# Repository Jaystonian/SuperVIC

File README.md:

# SuperVIC
The ultimate hobby computer

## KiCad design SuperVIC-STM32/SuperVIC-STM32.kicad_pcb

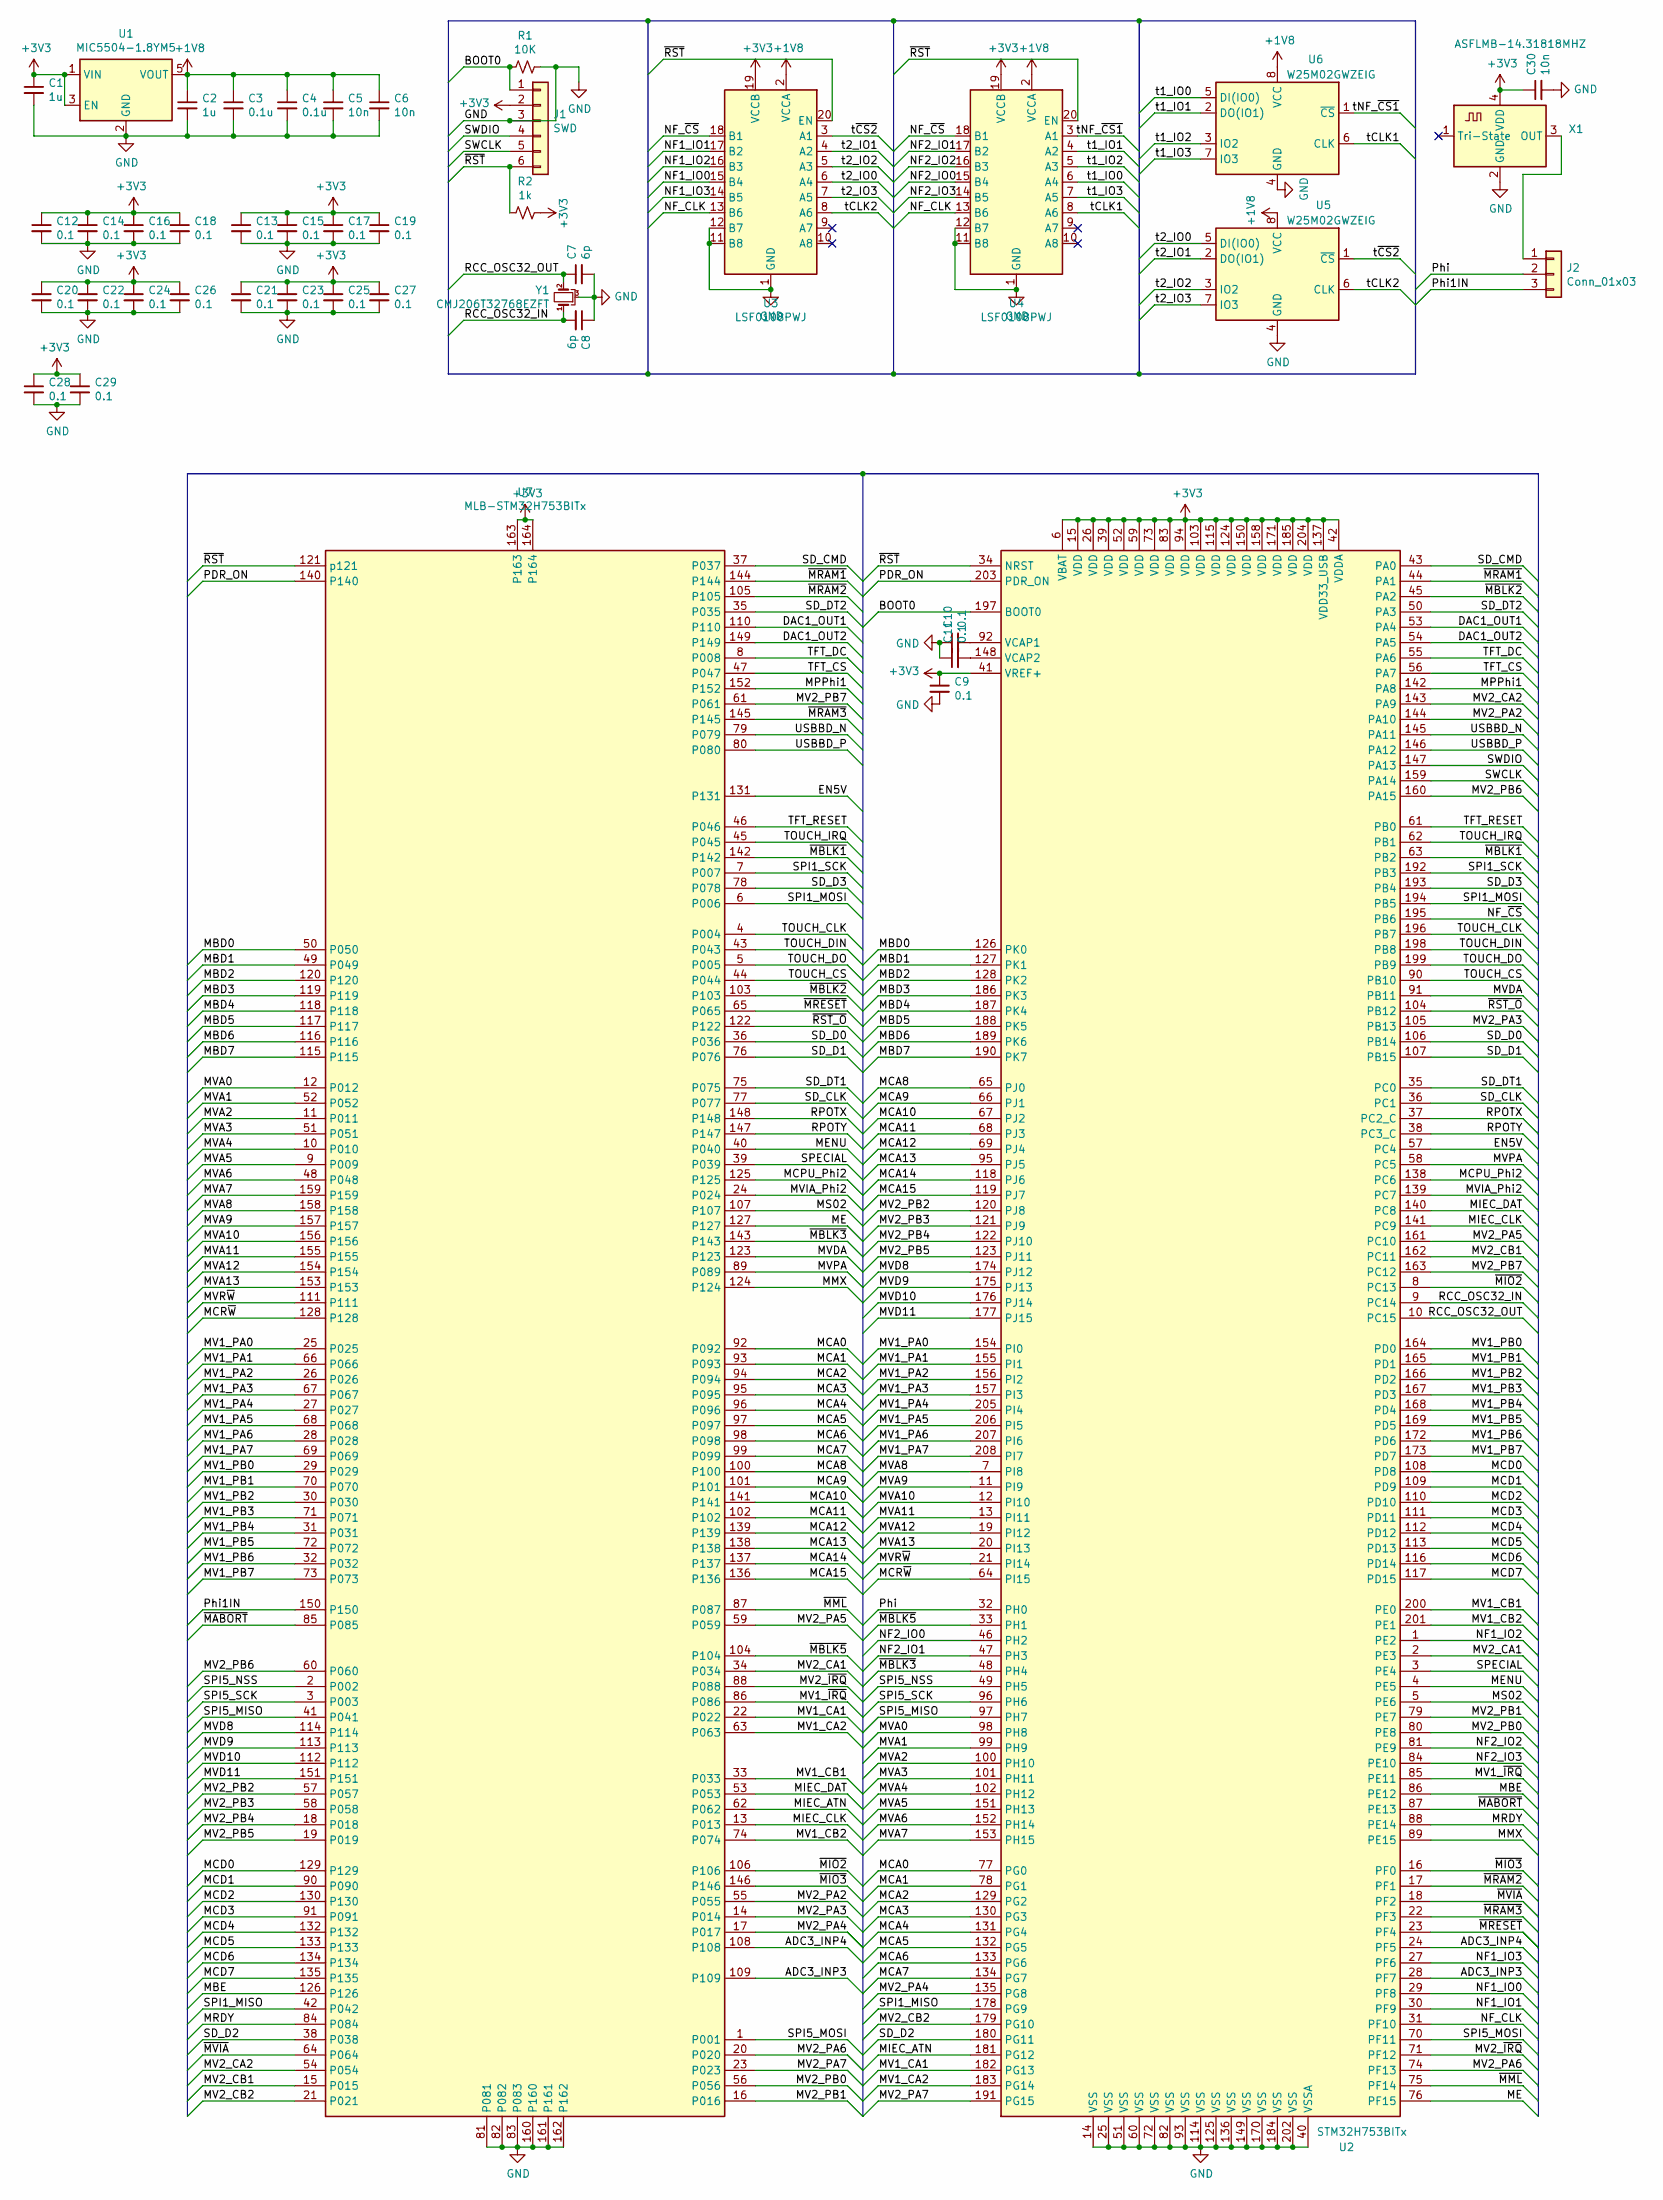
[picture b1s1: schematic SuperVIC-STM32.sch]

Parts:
C1, C2: 1u; C_0805_2012Metric_Pad1.15x1.40mm_HandSolder
C3, C4: 0.1u; C_0805_2012Metric_Pad1.15x1.40mm_HandSolder
C5, C6, C30: 10n; C_0805_2012Metric_Pad1.15x1.40mm_HandSolder
C7, C8: 6p; C_0805_2012Metric_Pad1.15x1.40mm_HandSolder
C9, C10, C11, C12, C13, C14, C15, C16, C17, C18, C19, C20, C21, C22, C23, C24, C25, C26, C27, C28, C29: 0.1; C_0805_2012Metric_Pad1.15x1.40mm_HandSolder
J1: SWD; PinHeader_1x06_P2.54mm_Vertical
J2: Conn_01x03; PinHeader_1x03_P2.54mm_Horizontal
R1: 10K; R_0805_2012Metric_Pad1.15x1.40mm_HandSolder
R2: 1k; R_0805_2012Metric_Pad1.15x1.40mm_HandSolder
U1: MIC5504-1.8YM5; SOT-23-5
U2: STM32H753BITx; LQFP-208_28x28mm_P0.5mm
U3, U4: LSF0108PWJ; TSSOP-20_4.4x6.5mm_P0.65mm
U5, U6: W25M02GWZEIG; WSON-8_8x6mm
U7: MLB-STM32H753BITx
X1: ASFLMB-14.31818MHZ; Oscillator_SMD_Abracon_ASF-4Pin_5.0x3.2mm_Handsoldering
Y1: CMJ206T32768EZFT; Crystal_SMD_CMJ206T

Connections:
+1V8: C2.1, C3.1, C4.1, C5.1, C6.1, U1.5 (VOUT), U3.2 (VCCA), U4.2 (VCCA), U5.8 (VCC), U6.8 (VCC)
+3V3: C1.1, C9.1, C12.1, C13.1, C14.1, C15.1, C16.1, C17.1, C18.1, C19.1, C20.1, C21.1, C22.1, C23.1, C24.1, C25.1, C26.1, C27.1, C28.1, C29.1, C30.1, J1.2, R2.1, U1.1 (VIN), U1.3 (EN), U2.6 (VBAT), U2.15 (VDD), U2.26 (VDD), U2.39 (VDD), U2.41 (VREF+), U2.42 (VDDA), U2.52 (VDD), U2.59 (VDD), U2.73 (VDD), U2.83 (VDD), U2.94 (VDD), U2.103 (VDD), U2.115 (VDD), U2.124 (VDD), U2.137 (VDD33_USB), U2.150 (VDD), U2.158 (VDD), U2.171 (VDD), U2.185 (VDD), U2.204 (VDD), U3.19 (VCCB), U4.19 (VCCB), U7.163, U7.164, X1.4 (VDD)
/ADC3_INP3: U2.28 (PF7), U7.109
/ADC3_INP4: U2.24 (PF5), U7.108
/BOOT0: J1.1, R1.2, U2.197 (BOOT0)
/DAC1_OUT1: U2.53 (PA4), U7.110
/DAC1_OUT2: U2.54 (PA5), U7.149
/EN5V: U2.57 (PC4), U7.131
/MBD0: U2.126 (PK0), U7.50
/MBD1: U2.127 (PK1), U7.49
/MBD2: U2.128 (PK2), U7.120
/MBD3: U2.186 (PK3), U7.119
/MBD4: U2.187 (PK4), U7.118
/MBD5: U2.188 (PK5), U7.117
/MBD6: U2.189 (PK6), U7.116
/MBD7: U2.190 (PK7), U7.115
/MBE: U2.86 (PE12), U7.126
/MCA0: U2.77 (PG0), U7.92
/MCA1: U2.78 (PG1), U7.93
/MCA2: U2.129 (PG2), U7.94
/MCA3: U2.130 (PG3), U7.95
/MCA4: U2.131 (PG4), U7.96
/MCA5: U2.132 (PG5), U7.97
/MCA6: U2.133 (PG6), U7.98
/MCA7: U2.134 (PG7), U7.99
/MCA8: U2.65 (PJ0), U7.100
/MCA9: U2.66 (PJ1), U7.101
/MCA10: U2.67 (PJ2), U7.141
/MCA11: U2.68 (PJ3), U7.102
/MCA12: U2.69 (PJ4), U7.139
/MCA13: U2.95 (PJ5), U7.138
/MCA14: U2.118 (PJ6), U7.137
/MCA15: U2.119 (PJ7), U7.136
/MCD0: U2.108 (PD8), U7.129
/MCD1: U2.109 (PD9), U7.90
/MCD2: U2.110 (PD10), U7.130
/MCD3: U2.111 (PD11), U7.91
/MCD4: U2.112 (PD12), U7.132
/MCD5: U2.113 (PD13), U7.133
/MCD6: U2.116 (PD14), U7.134
/MCD7: U2.117 (PD15), U7.135
/MCPU_Phi2: U2.138 (PC6), U7.125
/MCR~W: U2.64 (PI15), U7.128
/ME: U2.76 (PF15), U7.127
/MENU: U2.4 (PE5), U7.40
/MIEC_ATN: U2.181 (PG12), U7.62
/MIEC_CLK: U2.141 (PC9), U7.13
/MIEC_DAT: U2.140 (PC8), U7.53
/MMX: U2.89 (PE15), U7.124
/MPPhi1: U2.142 (PA8), U7.152
/MRDY: U2.88 (PE14), U7.84
/MS02: U2.5 (PE6), U7.107
/MV1_CA1: U2.182 (PG13), U7.22
/MV1_CA2: U2.183 (PG14), U7.63
/MV1_CB1: U2.200 (PE0), U7.33
/MV1_CB2: U2.201 (PE1), U7.74
/MV1_PA0: U2.154 (PI0), U7.25
/MV1_PA1: U2.155 (PI1), U7.66
/MV1_PA2: U2.156 (PI2), U7.26
/MV1_PA3: U2.157 (PI3), U7.67
/MV1_PA4: U2.205 (PI4), U7.27
/MV1_PA5: U2.206 (PI5), U7.68
/MV1_PA6: U2.207 (PI6), U7.28
/MV1_PA7: U2.208 (PI7), U7.69
/MV1_PB0: U2.164 (PD0), U7.29
/MV1_PB1: U2.165 (PD1), U7.70
/MV1_PB2: U2.166 (PD2), U7.30
/MV1_PB3: U2.167 (PD3), U7.71
/MV1_PB4: U2.168 (PD4), U7.31
/MV1_PB5: U2.169 (PD5), U7.72
/MV1_PB6: U2.172 (PD6), U7.32
/MV1_PB7: U2.173 (PD7), U7.73
/MV1_~IRQ: U2.85 (PE11), U7.86
/MV2_CA1: U2.2 (PE3), U7.34
/MV2_CA2: U2.143 (PA9), U7.54
/MV2_CB1: U2.162 (PC11), U7.15
/MV2_CB2: U2.179 (PG10), U7.21
/MV2_PA2: U2.144 (PA10), U7.55
/MV2_PA3: U2.105 (PB13), U7.14
/MV2_PA4: U2.135 (PG8), U7.17
/MV2_PA5: U2.161 (PC10), U7.59
/MV2_PA6: U2.74 (PF13), U7.20
/MV2_PA7: U2.191 (PG15), U7.23
/MV2_PB0: U2.80 (PE8), U7.56
/MV2_PB1: U2.79 (PE7), U7.16
/MV2_PB2: U2.120 (PJ8), U7.57
/MV2_PB3: U2.121 (PJ9), U7.58
/MV2_PB4: U2.122 (PJ10), U7.18
/MV2_PB5: U2.123 (PJ11), U7.19
/MV2_PB6: U2.160 (PA15), U7.60
/MV2_PB7: U2.163 (PC12), U7.61
/MV2_~IRQ: U2.71 (PF12), U7.88
/MVA0: U2.98 (PH8), U7.12
/MVA1: U2.99 (PH9), U7.52
/MVA2: U2.100 (PH10), U7.11
/MVA3: U2.101 (PH11), U7.51
/MVA4: U2.102 (PH12), U7.10
/MVA5: U2.151 (PH13), U7.9
/MVA6: U2.152 (PH14), U7.48
/MVA7: U2.153 (PH15), U7.159
/MVA8: U2.7 (PI8), U7.158
/MVA9: U2.11 (PI9), U7.157
/MVA10: U2.12 (PI10), U7.156
/MVA11: U2.13 (PI11), U7.155
/MVA12: U2.19 (PI12), U7.154
/MVA13: U2.20 (PI13), U7.153
/MVD8: U2.174 (PJ12), U7.114
/MVD9: U2.175 (PJ13), U7.113
/MVD10: U2.176 (PJ14), U7.112
/MVD11: U2.177 (PJ15), U7.151
/MVDA: U2.91 (PB11), U7.123
/MVIA_Phi2: U2.139 (PC7), U7.24
/MVPA: U2.58 (PC5), U7.89
/MVR~W: U2.21 (PI14), U7.111
/NF1_IO0: U2.29 (PF8), U3.15 (B4)
/NF1_IO1: U2.30 (PF9), U3.17 (B2)
/NF1_IO2: U2.1 (PE2), U3.16 (B3)
/NF1_IO3: U2.27 (PF6), U3.14 (B5)
/NF2_IO0: U2.46 (PH2), U4.15 (B4)
/NF2_IO1: U2.47 (PH3), U4.17 (B2)
/NF2_IO2: U2.81 (PE9), U4.16 (B3)
/NF2_IO3: U2.84 (PE10), U4.14 (B5)
/NF_CLK: U2.31 (PF10), U3.13 (B6), U4.13 (B6)
/NF_~CS: U2.195 (PB6), U3.18 (B1), U4.18 (B1)
/PDR_ON: U2.203 (PDR_ON), U7.140
/Phi: J2.2, U2.32 (PH0)
/Phi1IN: J2.3, U7.150
/RCC_OSC32_IN: C8.2, U2.9 (PC14), Y1.1
/RCC_OSC32_OUT: C7.1, U2.10 (PC15), Y1.2
/RPOTX: U2.37 (PC2_C), U7.148
/RPOTY: U2.38 (PC3_C), U7.147
/SD_CLK: U2.36 (PC1), U7.77
/SD_CMD: U2.43 (PA0), U7.37
/SD_D0: U2.106 (PB14), U7.36
/SD_D1: U2.107 (PB15), U7.76
/SD_D2: U2.180 (PG11), U7.38
/SD_D3: U2.193 (PB4), U7.78
/SD_DT1: U2.35 (PC0), U7.75
/SD_DT2: U2.50 (PA3), U7.35
/SPECIAL: U2.3 (PE4), U7.39
/SPI1_MISO: U2.178 (PG9), U7.42
/SPI1_MOSI: U2.194 (PB5), U7.6
/SPI1_SCK: U2.192 (PB3), U7.7
/SPI5_MISO: U2.97 (PH7), U7.41
/SPI5_MOSI: U2.70 (PF11), U7.1
/SPI5_NSS: U2.49 (PH5), U7.2
/SPI5_SCK: U2.96 (PH6), U7.3
/SWCLK: J1.5, U2.159 (PA14)
/SWDIO: J1.4, U2.147 (PA13)
/TFT_CS: U2.56 (PA7), U7.47
/TFT_DC: U2.55 (PA6), U7.8
/TFT_RESET: U2.61 (PB0), U7.46
/TOUCH_CLK: U2.196 (PB7), U7.4
/TOUCH_CS: U2.90 (PB10), U7.44
/TOUCH_DIN: U2.198 (PB8), U7.43
/TOUCH_DO: U2.199 (PB9), U7.5
/TOUCH_IRQ: U2.62 (PB1), U7.45
/USBBD_N: U2.145 (PA11), U7.79
/USBBD_P: U2.146 (PA12), U7.80
/t1_IO0: U4.6 (A4), U6.5 (DI(IO0))
/t1_IO1: U4.4 (A2), U6.2 (DO(IO1))
/t1_IO2: U4.5 (A3), U6.3 (IO2)
/t1_IO3: U4.7 (A5), U6.7 (IO3)
/t2_IO0: U3.6 (A4), U5.5 (DI(IO0))
/t2_IO1: U3.4 (A2), U5.2 (DO(IO1))
/t2_IO2: U3.5 (A3), U5.3 (IO2)
/t2_IO3: U3.7 (A5), U5.7 (IO3)
/tCLK1: U4.8 (A6), U6.6 (CLK)
/tCLK2: U3.8 (A6), U5.6 (CLK)
/tNF_~CS1: U4.3 (A1), U6.1 (~CS)
/t~CS2: U3.3 (A1), U5.1 (~CS)
/~MABORT: U2.87 (PE13), U7.85
/~MBLK1: U2.63 (PB2), U7.142
/~MBLK2: U2.45 (PA2), U7.103
/~MBLK3: U2.48 (PH4), U7.143
/~MBLK5: U2.33 (PH1), U7.104
/~MIO2: U2.8 (PC13), U7.106
/~MIO3: U2.16 (PF0), U7.146
/~MML: U2.75 (PF14), U7.87
/~MRAM1: U2.44 (PA1), U7.144
/~MRAM2: U2.17 (PF1), U7.105
/~MRAM3: U2.22 (PF3), U7.145
/~MRESET: U2.23 (PF4), U7.65
/~MVIA: U2.18 (PF2), U7.64
/~RST: J1.6, R2.2, U2.34 (NRST), U3.20 (EN), U4.20 (EN), U7.121 (p121)
/~RST_O: U2.104 (PB12), U7.122
GND: C1.2, C2.2, C3.2, C4.2, C5.2, C6.2, C7.2, C8.1, C9.2, C10.1, C11.1, C12.2, C13.2, C14.2, C15.2, C16.2, C17.2, C18.2, C19.2, C20.2, C21.2, C22.2, C23.2, C24.2, C25.2, C26.2, C27.2, C28.2, C29.2, C30.2, J1.3, R1.1, U1.2 (GND), U2.14 (VSS), U2.25 (VSS), U2.40 (VSSA), U2.51 (VSS), U2.60 (VSS), U2.72 (VSS), U2.82 (VSS), U2.93 (VSS), U2.114 (VSS), U2.125 (VSS), U2.136 (VSS), U2.149 (VSS), U2.170 (VSS), U2.184 (VSS), U2.202 (VSS), U3.1 (GND), U3.11 (B8), U3.12 (B7), U4.1 (GND), U4.11 (B8), U4.12 (B7), U5.4 (GND), U6.4 (GND), U7.81, U7.82, U7.83, U7.160, U7.161, U7.162, X1.2 (GND), Y1.3
unnamed: C10.2, U2.92 (VCAP1)
unnamed: C11.2, U2.148 (VCAP2)
unnamed: J2.1, X1.3 (OUT)

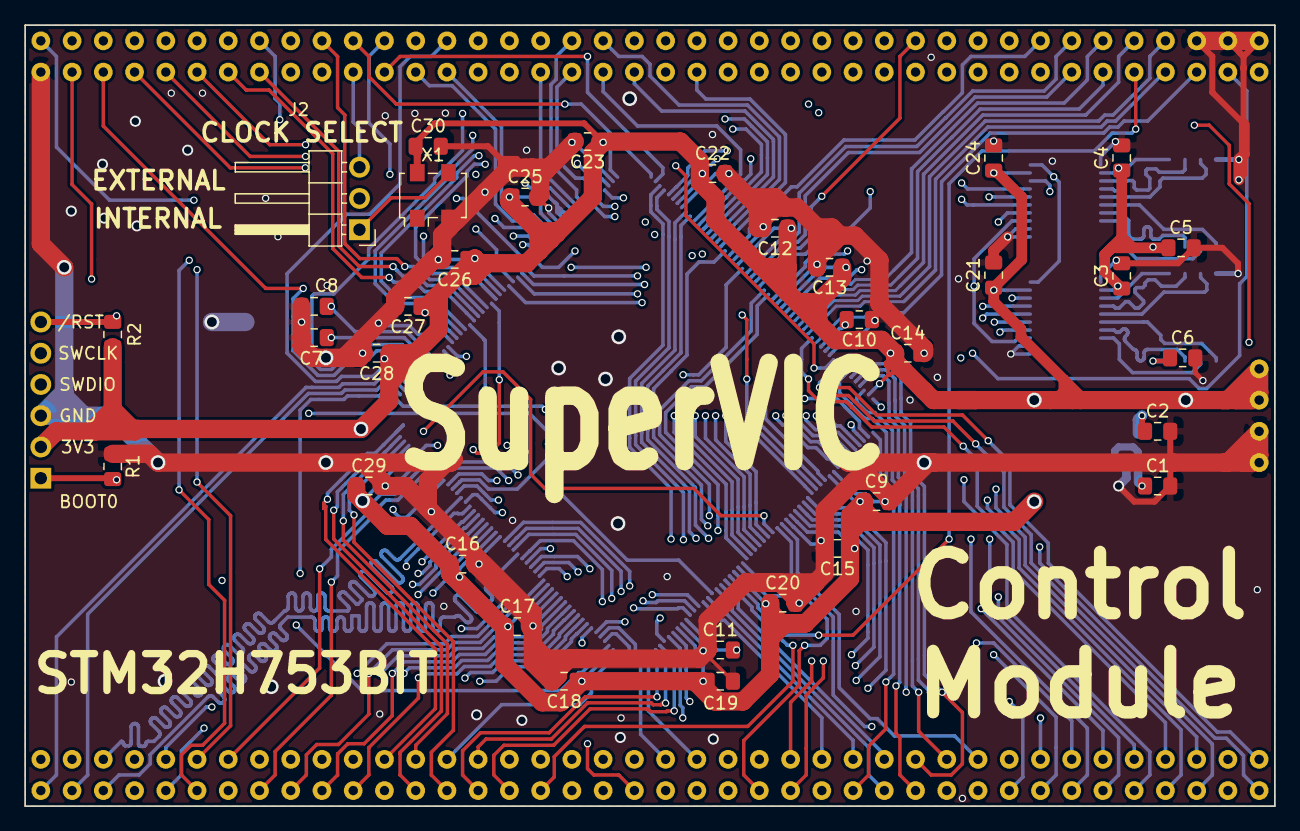
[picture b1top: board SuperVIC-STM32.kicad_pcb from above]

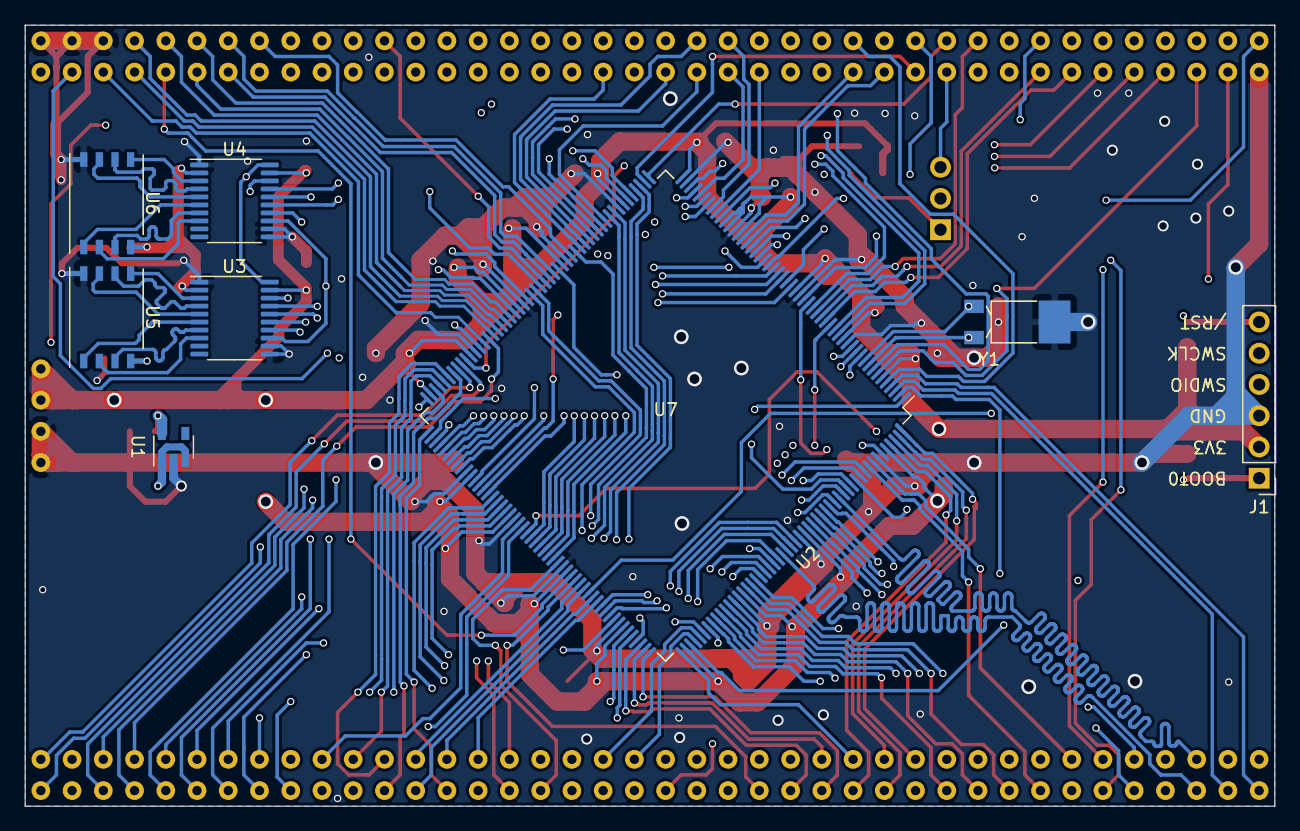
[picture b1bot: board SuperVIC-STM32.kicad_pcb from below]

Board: 4 copper layers, 101.6 x 63.5 mm, 43 parts (8 on the bottom side), 190 nets.

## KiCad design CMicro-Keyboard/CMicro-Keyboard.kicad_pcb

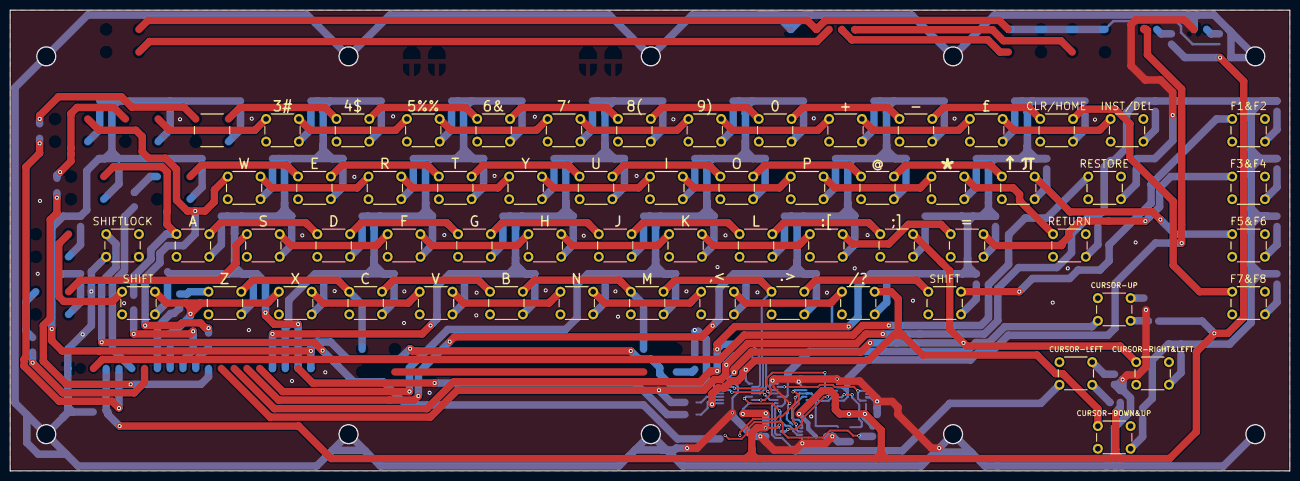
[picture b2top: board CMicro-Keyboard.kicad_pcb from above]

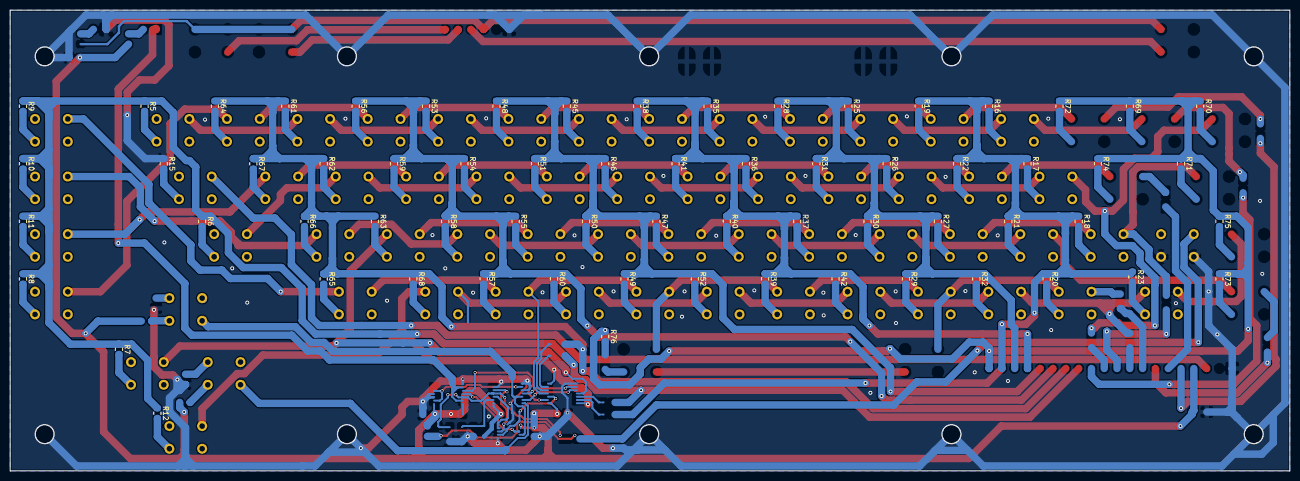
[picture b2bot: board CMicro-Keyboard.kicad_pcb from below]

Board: 2 copper layers, 254.0 x 91.4 mm, 126 parts (65 on the bottom side), 74 nets.

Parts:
R5, R6, R7, R8, R9, R10, R11, R12, R15, R16, R17, R18, R19, R20, R21, R22, R23, R25, R26, R27, R28, R29, R30, R31, R32, R35, R36, R37, R38, R39, R40, R41, R42, R45, R46, R47, R48, R49, R50, R51, R52, R53, R54, R55, R56, R57, R58, R59, R60, R61, R62, R63, R64, R65, R66, R67, R68, R69, R70, R71, R72, R73, R74, R75, R76: 120R; R_0805_2012Metric_Pad1.15x1.40mm_HandSolder
SW0103-Restore1, SW1305-F7-key1, SW1306-F5-key1, SW1307-F3-key1, SW1308-F1-Key1, SW1309-CrsrUD1, SW1309-CrsrUp1, SW1310-CrsrLR1, SW1310-CrsrLeft1, SW1311-Return1, SW1312-InstDel1, SW1405-ClrHome1, SW1406-UpArrow1, SW1407-Key=1, SW1408-RShift1, SW1409-Key/1, SW1410-Key;1, SW1411-Key*1, SW1412-KeyPound1, SW1505-Key-1, SW1506-Key@1, SW1507-Key:1, SW1508-Key.1, SW1509-Key,1, SW1510-KeyL1, SW1511-KeyP1, SW1512-Key+1, SW1605-0-key1, SW1606-KeyO1, SW1607-KeyK1, SW1608-KeyM1, SW1609-KeyN1, SW1610-KeyJ1, SW1611-KeyI1, SW1612-9-key1, SW1705-8-key1, SW1706-KeyU1, SW1707-KeyH1, SW1708-KeyB1, SW1709-KeyV1, SW1710-KeyG1, SW1711-KeyY1, SW1712-7-key1, SW1805-6-key1, SW1806-KeyT1, SW1807-F-key1, SW1808-KeyC1, SW1809-KeyX1, SW1810-KeyD1, SW1811-KeyR1, SW1812-5-key1, SW1905-4-key1, SW1906-KeyE1, SW1907-KeyS1, SW1908-KeyZ1, SW1909&2501-ShiftCapsLock1, SW1909-LShift1, SW1910-KeyA1, SW1911-KeyW1, SW1912-3-key1, SW2005-2-key1: SW_Push; SW_PUSH_6mm_H8mm

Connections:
/P05: SW1305-F7-key1.1, SW1405-ClrHome1.1, SW1505-Key-1.1, SW1605-0-key1.1, SW1705-8-key1.1, SW1805-6-key1.1, SW1905-4-key1.1
/P06: SW1306-F5-key1.1, SW1406-UpArrow1.1, SW1506-Key@1.1, SW1606-KeyO1.1, SW1706-KeyU1.1, SW1806-KeyT1.1, SW1906-KeyE1.1
/P07: SW1307-F3-key1.1, SW1407-Key=1.1, SW1507-Key:1.1, SW1607-KeyK1.1, SW1707-KeyH1.1, SW1807-F-key1.1, SW1907-KeyS1.1
/P08: SW1308-F1-Key1.1, SW1408-RShift1.1, SW1508-Key.1.1, SW1608-KeyM1.1, SW1708-KeyB1.1, SW1808-KeyC1.1, SW1908-KeyZ1.1
/P09: SW1309-CrsrUD1.1, SW1409-Key/1.1, SW1509-Key,1.1, SW1609-KeyN1.1, SW1709-KeyV1.1, SW1809-KeyX1.1, SW1909-LShift1.1
/P10: SW1310-CrsrLR1.1, SW1410-Key;1.1, SW1510-KeyL1.1, SW1610-KeyJ1.1, SW1710-KeyG1.1, SW1810-KeyD1.1, SW1910-KeyA1.1
/P11: SW1311-Return1.1, SW1411-Key*1.1, SW1511-KeyP1.1, SW1611-KeyI1.1, SW1711-KeyY1.1, SW1811-KeyR1.1, SW1911-KeyW1.1
/P12: SW1312-InstDel1.1, SW1412-KeyPound1.1, SW1512-Key+1.1, SW1612-9-key1.1, SW1712-7-key1.1, SW1812-5-key1.1, SW1912-3-key1.1
/P13: R5.1, R6.1, R7.1, R8.1, R9.1, R10.1, R11.1, R12.1
/P14: R61.1, R62.1, R63.1, R64.1, R65.1, R66.1, R67.1, R68.1
/P15: R53.1, R54.1, R55.1, R56.1, R57.1, R58.1, R59.1, R60.1
/P16: R45.1, R46.1, R47.1, R48.1, R49.1, R50.1, R51.1, R52.1
/P17: R35.1, R36.1, R37.1, R38.1, R39.1, R40.1, R41.1, R42.1
/P18: R25.1, R26.1, R27.1, R28.1, R29.1, R30.1, R31.1, R32.1
/P19: R16.1, R17.1, R18.1, R19.1, R20.1, R21.1, R22.1, R23.1
/P20: R69.1, R70.1, R71.1, R72.1, R73.1, R74.1, R75.1, R76.1
GND: R15.1, SW1909&2501-ShiftCapsLock1.2
unnamed: R5.2, SW1312-InstDel1.2
unnamed: R6.2, SW1311-Return1.2
unnamed: R7.2, SW1310-CrsrLR1.2
unnamed: R8.2, SW1305-F7-key1.2
unnamed: R9.2, SW1308-F1-Key1.2
unnamed: R10.2, SW1307-F3-key1.2
unnamed: R11.2, SW1306-F5-key1.2
unnamed: R12.2, SW1309-CrsrUD1.2
unnamed: R15.2, SW0103-Restore1.2
unnamed: R16.2, SW1912-3-key1.2
unnamed: R17.2, SW1911-KeyW1.2
unnamed: R18.2, SW1910-KeyA1.2
unnamed: R19.2, SW1905-4-key1.2
unnamed: R20.2, SW1908-KeyZ1.2
unnamed: R21.2, SW1907-KeyS1.2
unnamed: R22.2, SW1906-KeyE1.2
unnamed: R23.2, SW1909-LShift1.2
unnamed: R25.2, SW1812-5-key1.2
unnamed: R26.2, SW1811-KeyR1.2
unnamed: R27.2, SW1810-KeyD1.2
unnamed: R28.2, SW1805-6-key1.2
unnamed: R29.2, SW1808-KeyC1.2
unnamed: R30.2, SW1807-F-key1.2
unnamed: R31.2, SW1806-KeyT1.2
unnamed: R32.2, SW1809-KeyX1.2
unnamed: R35.2, SW1712-7-key1.2
unnamed: R36.2, SW1711-KeyY1.2
unnamed: R37.2, SW1710-KeyG1.2
unnamed: R38.2, SW1705-8-key1.2
unnamed: R39.2, SW1708-KeyB1.2
unnamed: R40.2, SW1707-KeyH1.2
unnamed: R41.2, SW1706-KeyU1.2
unnamed: R42.2, SW1709-KeyV1.2
unnamed: R45.2, SW1612-9-key1.2
unnamed: R46.2, SW1611-KeyI1.2
unnamed: R47.2, SW1610-KeyJ1.2
unnamed: R48.2, SW1605-0-key1.2
unnamed: R49.2, SW1608-KeyM1.2
unnamed: R50.2, SW1607-KeyK1.2
unnamed: R51.2, SW1606-KeyO1.2
unnamed: R52.2, SW1609-KeyN1.2
unnamed: R53.2, SW1512-Key+1.2
unnamed: R54.2, SW1511-KeyP1.2
unnamed: R55.2, SW1510-KeyL1.2
unnamed: R56.2, SW1505-Key-1.2
unnamed: R57.2, SW1508-Key.1.2
unnamed: R58.2, SW1507-Key:1.2
unnamed: R59.2, SW1506-Key@1.2
unnamed: R60.2, SW1509-Key,1.2
unnamed: R61.2, SW1412-KeyPound1.2
unnamed: R62.2, SW1411-Key*1.2
unnamed: R63.2, SW1410-Key;1.2
unnamed: R64.2, SW1405-ClrHome1.2
unnamed: R65.2, SW1408-RShift1.2
unnamed: R66.2, SW1407-Key=1.2
unnamed: R67.2, SW1406-UpArrow1.2
unnamed: R68.2, SW1409-Key/1.2
